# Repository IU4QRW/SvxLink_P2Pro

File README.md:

# SvxLink_P2Pro
SvxLink for Armsom p2pro

# Risorse:
Pagina prodotto https://www.armsom.org/p2pro

Google Drive Armsom https://drive.google.com/drive/folders/1x2KOX1F4-DVyyV_9qfdH28PWIORcWH56

Wiki Armsom https://docs.armsom.org/armsom-p2pro

https://forum.armsom.org/t/rk-sdk-debian-system-is-blocked/222

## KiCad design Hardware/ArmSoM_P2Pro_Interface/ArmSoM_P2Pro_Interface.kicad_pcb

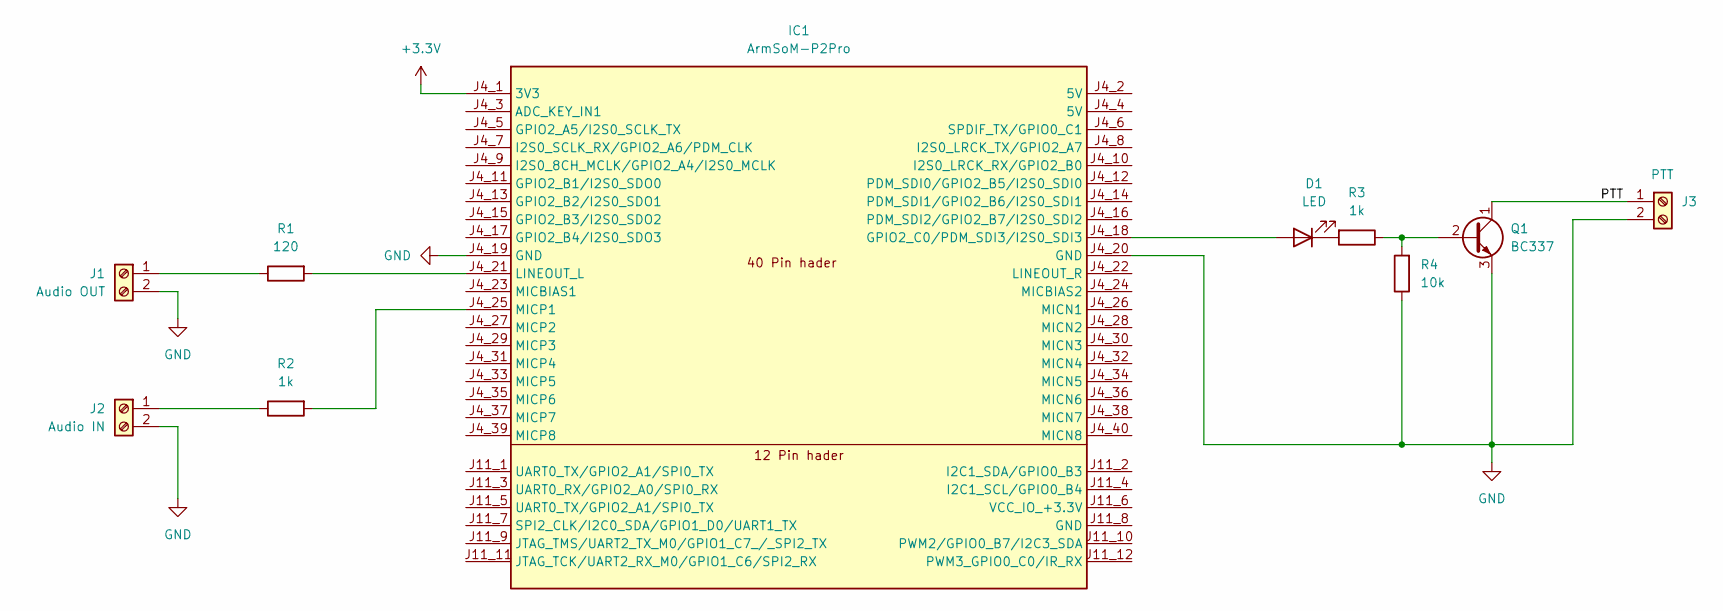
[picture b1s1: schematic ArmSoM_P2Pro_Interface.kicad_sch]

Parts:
D1: LED; LED_D3.0mm
IC1: ArmSoM-P2Pro; ArmSom-P2Pro
J1: Audio OUT; TerminalBlock_Phoenix_MPT-0,5-2-2.54_1x02_P2.54mm_Horizontal
J2: Audio IN; TerminalBlock_Phoenix_MPT-0,5-2-2.54_1x02_P2.54mm_Horizontal
J3: PTT; TerminalBlock_Phoenix_MPT-0,5-2-2.54_1x02_P2.54mm_Horizontal
Q1: BC337; TO-92_Inline
R1: 120; R_Axial_DIN0207_L6.3mm_D2.5mm_P10.16mm_Horizontal
R2, R3: 1k; R_Axial_DIN0207_L6.3mm_D2.5mm_P10.16mm_Horizontal
R4: 10k; R_Axial_DIN0207_L6.3mm_D2.5mm_P10.16mm_Horizontal

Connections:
+3.3V: IC1.J4_1 (3V3)
/PTT: J3.1, Q1.1 (C)
GND: IC1.J4_19 (GND), IC1.J4_20 (GND), J1.2, J2.2, J3.2, Q1.3 (E), R4.1
unnamed: D1.2 (A), IC1.J4_18 (GPIO2_C0/PDM_SDI3/I2S0_SDI3)
unnamed: D1.1 (K), R3.2
unnamed: IC1.J4_21 (LINEOUT_L), R1.2
unnamed: IC1.J4_25 (MICP1), R2.2
unnamed: J1.1, R1.1
unnamed: J2.1, R2.1
unnamed: Q1.2 (B), R3.1, R4.2

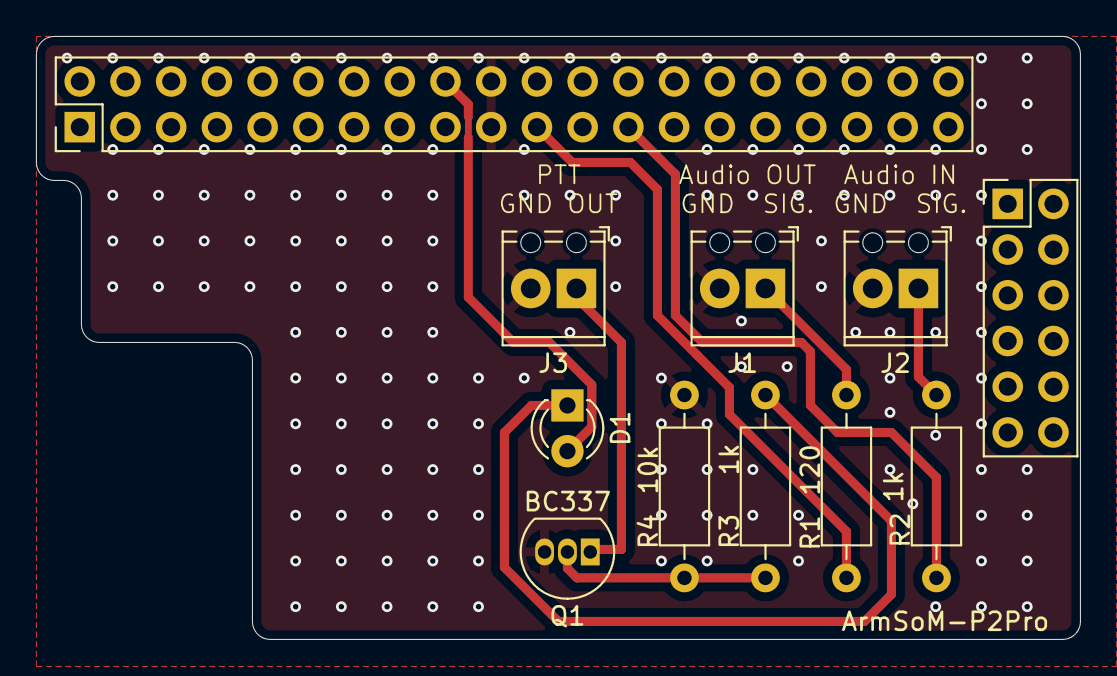
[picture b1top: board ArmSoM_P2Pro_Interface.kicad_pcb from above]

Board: 2 copper layers, 58.0 x 33.5 mm, 10 parts (0 on the bottom side), 9 nets.

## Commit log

2024-08-23 Prova Git
